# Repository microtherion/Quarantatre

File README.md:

# Quarantatre
Design for ATtiny43U breakout board. See http://samelimmat.blogspot.com/2015/04/introducing-quarantatre.html

Boards can be ordered at OSHPark: https://oshpark.com/shared_projects/7uvGe7Xo

<br />This work is licensed under a <a rel="license" href="http://creativecommons.org/licenses/by/4.0/">Creative Commons Attribution 4.0 International License</a>.

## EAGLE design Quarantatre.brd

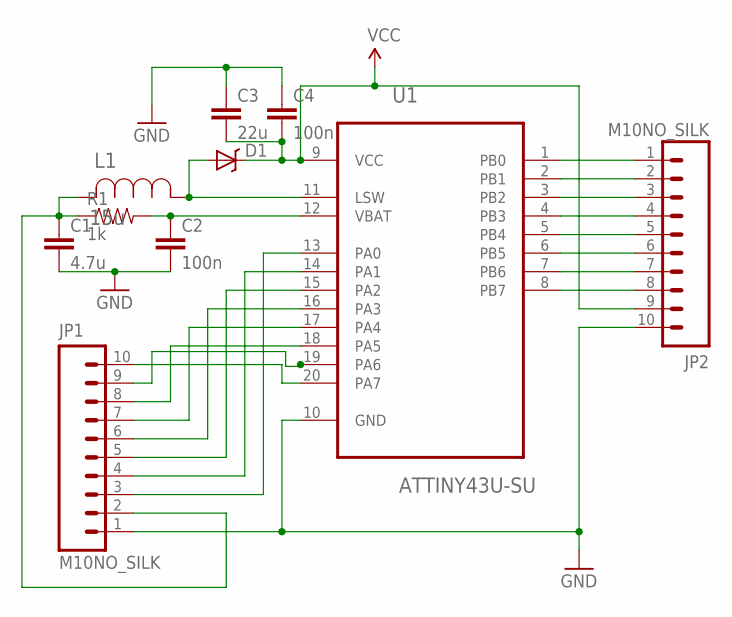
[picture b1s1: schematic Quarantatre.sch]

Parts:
C1: 4.7u; C0805
C2, C4: 100n; 0603-CAP
C3: 22u; C0805
D1: BAT20JFILM; SOD-323
JP1, JP2: M10NO_SILK; 1X10_NO_SILK
L1: 15u; IND4040
R1: 1k; 0603-RES
U1: ATTINY43U-SU; SOIC127P1032X265-20N

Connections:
GND: C1.2, C2.2, C3.1, C4.1, JP1.1, JP2.10, U1.10 (GND)
unnamed: C1.1, JP1.2, L1.P$2 (2), R1.1
unnamed: C2.1, R1.2, U1.12 (VBAT)
unnamed: D1.2 (A), L1.P$1 (1), U1.11 (LSW)
unnamed: JP1.9, U1.19 (PA6)
unnamed: JP1.3, U1.13 (PA0)
unnamed: JP1.4, U1.14 (PA1)
unnamed: JP2.1, U1.1 (PB0)
unnamed: JP2.2, U1.2 (PB1)
unnamed: JP2.3, U1.3 (PB2)
unnamed: JP2.4, U1.4 (PB3)
unnamed: JP2.5, U1.5 (PB4)
unnamed: JP2.6, U1.6 (PB5)
unnamed: JP2.7, U1.7 (PB6)
unnamed: JP2.8, U1.8 (PB7)
unnamed: JP1.5, U1.15 (PA2)
unnamed: JP1.6, U1.16 (PA3)
unnamed: JP1.7, U1.17 (PA4)
unnamed: JP1.8, U1.18 (PA5)
unnamed: JP1.10, U1.20 (PA7)
VCC: C3.2, C4.2, D1.1 (C), JP2.9, U1.9 (VCC)

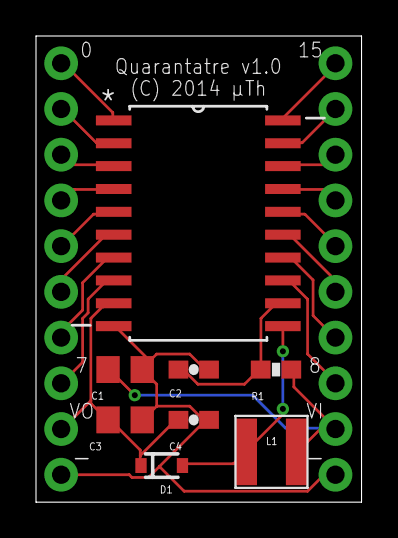
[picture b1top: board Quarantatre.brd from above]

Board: 2 copper layers, 18.1 x 25.9 mm, 10 parts (0 on the bottom side), 21 nets.

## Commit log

2015-04-04 Imported Quarantatre v1.0

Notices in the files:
Quarantatre.brd:
(C) 2014 µTh
parts and their libraries:
SparkFun-Passives: Licensing: CC v3.0 Share-Alike You are welcome to use this library for commercial purposes.
